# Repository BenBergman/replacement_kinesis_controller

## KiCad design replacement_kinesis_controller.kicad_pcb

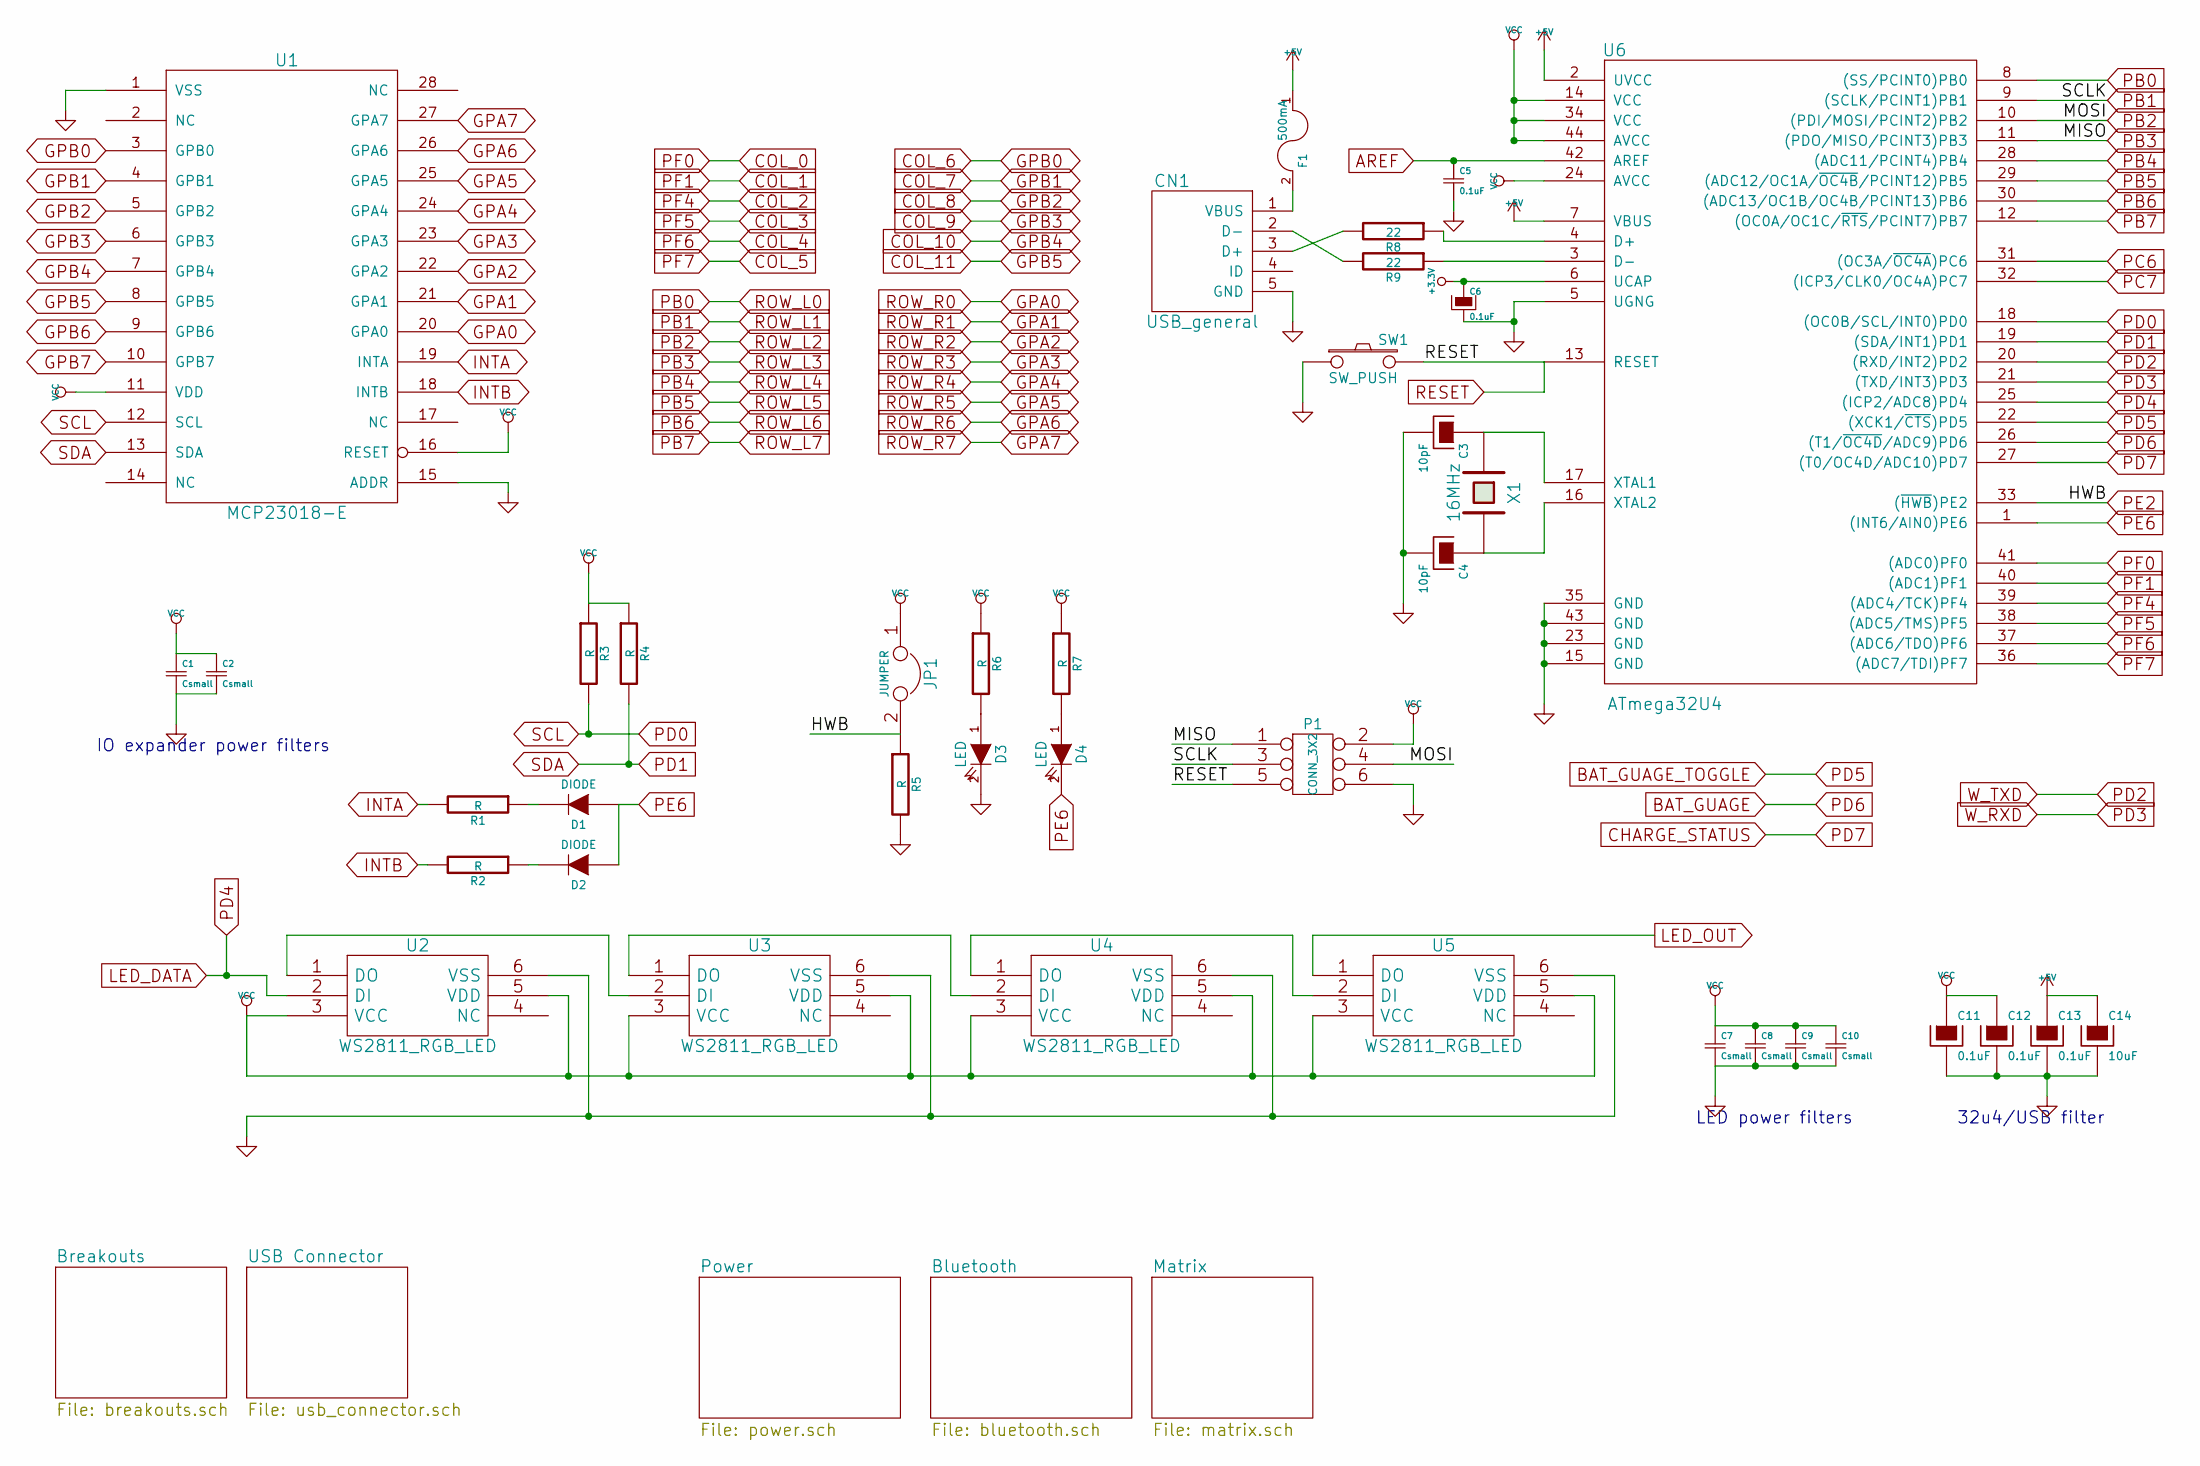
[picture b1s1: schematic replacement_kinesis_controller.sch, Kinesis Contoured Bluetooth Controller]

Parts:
C1, C2, C7, C8, C9, C10: Csmall; C_0805_HandSoldering
C3, C4: 10pF; C_0805_HandSoldering
C5, C6, C11, C12, C13: 0.1uF; C_0805_HandSoldering
C14: 10uF; C_0805_HandSoldering
CN1: USB_general; Pin_Header_Staggered_Straight_1x05
D1, D2: DIODE; SOD-323_Handsolder
D3, D4: LED; LED-0805
F1: 500mA; R_0805_HandSoldering
JP1: JUMPER; JUMPER_2
P1: CONN_3X2; Pin_Header_Staggered_Straight_2x03
R1, R2, R3, R4, R5, R6, R7: R; R_0805_HandSoldering
R8, R9: 22; R_0805_HandSoldering
SW1: SW_PUSH; SW_SPST_PTS645
U1: MCP23018-E; SOIC-28
U2, U3, U4, U5: WS2811_RGB_LED; LED_RGB_WS2811
U6: ATmega32U4; TQFP-44_10x10mm_Pitch0.8mm
X1: 16MHz; Crystal_HC49-SD_SMD

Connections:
+3.3V: C6.1, U6.6 (UCAP); also elsewhere on the board
+5V: C13.1, C14.1, F1.1, U6.2 (UVCC), U6.7 (VBUS); also elsewhere on the board
AREF: C5.1, U6.42 (AREF); also elsewhere on the board
BAT_GUAGE: U6.26 ((T1/~OC4D~/ADC9)PD6); also elsewhere on the board
BAT_GUAGE_TOGGLE: U6.22 ((XCK1/~CTS~)PD5); also elsewhere on the board
COL_0: U6.41 ((ADC0)PF0); also elsewhere on the board
COL_2: U6.39 ((ADC4/TCK)PF4); also elsewhere on the board
COL_5: U6.36 ((ADC7/TDI)PF7); also elsewhere on the board
COL_6: U1.3 (GPB0); also elsewhere on the board
COL_7: U1.4 (GPB1); also elsewhere on the board
COL_8: U1.5 (GPB2); also elsewhere on the board
COL_11: U1.8 (GPB5); also elsewhere on the board
GND: C1.2, C2.2, C3.2, C4.2, C5.2, C6.2, C7.2, C8.2, C9.2, C10.2, C11.2, C12.2, C13.2, C14.2, CN1.5 (GND), D3.2 (K), P1.6, R5.2, SW1.1, U1.1 (VSS), U1.15 (ADDR), U2.6 (VSS), U3.6 (VSS), U4.6 (VSS), U5.6 (VSS), U6.5 (UGNG), U6.15 (GND), U6.23 (GND), U6.35 (GND), U6.43 (GND); also elsewhere on the board
GPA3: U1.23 (GPA3); also elsewhere on the board
GPA5: U1.25 (GPA5); also elsewhere on the board
GPA6: U1.26 (GPA6); also elsewhere on the board
GPA7: U1.27 (GPA7); also elsewhere on the board
GPB3: U1.6 (GPB3); also elsewhere on the board
GPB4: U1.7 (GPB4); also elsewhere on the board
GPB6: U1.9 (GPB6); also elsewhere on the board
GPB7: U1.10 (GPB7); also elsewhere on the board
INTA: R1.2, U1.19 (INTA)
INTB: R2.2, U1.18 (INTB)
LED_OUT: U5.1 (DO); also elsewhere on the board
unnamed: C3.1, U6.17 (XTAL1), X1.1
unnamed: C4.1, U6.16 (XTAL2), X1.2
unnamed: CN1.1 (VBUS), F1.2
unnamed: CN1.2 (D-), R9.2
unnamed: CN1.3 (D+), R8.2
unnamed: D1.2 (K), R1.1
unnamed: D2.2 (K), R2.1
unnamed: D3.1 (A), R6.2
unnamed: D4.1 (A), R7.2
unnamed: R8.1, U6.4 (D+)
unnamed: R9.1, U6.3 (D-)
unnamed: U2.1 (DO), U3.2 (DI)
unnamed: U3.1 (DO), U4.2 (DI)
unnamed: U4.1 (DO), U5.2 (DI)
PB1: P1.3, U6.9 ((SCLK/PCINT1)PB1); also elsewhere on the board
PB2: P1.4, U6.10 ((PDI/MOSI/PCINT2)PB2); also elsewhere on the board
PB3: P1.1, U6.11 ((PDO/MISO/PCINT3)PB3); also elsewhere on the board
PB4: U6.28 ((ADC11/PCINT4)PB4); also elsewhere on the board
PB5: U6.29 ((ADC12/OC1A/~OC4B~/PCINT12)PB5); also elsewhere on the board
PB6: U6.30 ((ADC13/OC1B/OC4B/PCINT13)PB6); also elsewhere on the board
PB7: U6.12 ((OC0A/OC1C/~RTS~/PCINT7)PB7); also elsewhere on the board
PC6: U6.31 ((OC3A/~OC4A~)PC6); also elsewhere on the board
PC7: U6.32 ((ICP3/CLK0/OC4A)PC7); also elsewhere on the board
PD0: R3.2, U1.12 (SCL), U6.18 ((OC0B/SCL/INT0)PD0); also elsewhere on the board
PD3: U6.21 ((TXD/INT3)PD3); also elsewhere on the board
PD7: U6.27 ((T0/OC4D/ADC10)PD7); also elsewhere on the board
PE2: JP1.2, R5.1, U6.33 ((~HWB~)PE2)
PE6: D1.1 (A), D2.1 (A), D4.2 (K), U6.1 ((INT6/AIN0)PE6); also elsewhere on the board
PF1: U6.40 ((ADC1)PF1); also elsewhere on the board
PF5: U6.38 ((ADC5/TMS)PF5); also elsewhere on the board
PF6: U6.37 ((ADC6/TDO)PF6); also elsewhere on the board
RESET: P1.5, SW1.2, U6.13 (RESET); also elsewhere on the board
ROW_L0: U6.8 ((SS/PCINT0)PB0); also elsewhere on the board
ROW_R0: U1.20 (GPA0); also elsewhere on the board
ROW_R1: U1.21 (GPA1); also elsewhere on the board
ROW_R2: U1.22 (GPA2); also elsewhere on the board
ROW_R4: U1.24 (GPA4); also elsewhere on the board
SDA: R4.2, U1.13 (SDA), U6.19 ((SDA/INT1)PD1); also elsewhere on the board
VCC: C1.1, C2.1, C7.1, C8.1, C9.1, C10.1, C11.1, C12.1, JP1.1, P1.2, R3.1, R4.1, R6.1, R7.1, U1.11 (VDD), U1.16 (RESET), U2.3 (VCC), U2.5 (VDD), U3.3 (VCC), U3.5 (VDD), U4.3 (VCC), U4.5 (VDD), U5.3 (VCC), U5.5 (VDD), U6.14 (VCC), U6.24 (AVCC), U6.34 (VCC), U6.44 (AVCC); also elsewhere on the board
W_TXD: U6.20 ((RXD/INT2)PD2); also elsewhere on the board

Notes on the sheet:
32u4/USB filter
LED power filters
IO expander power filters

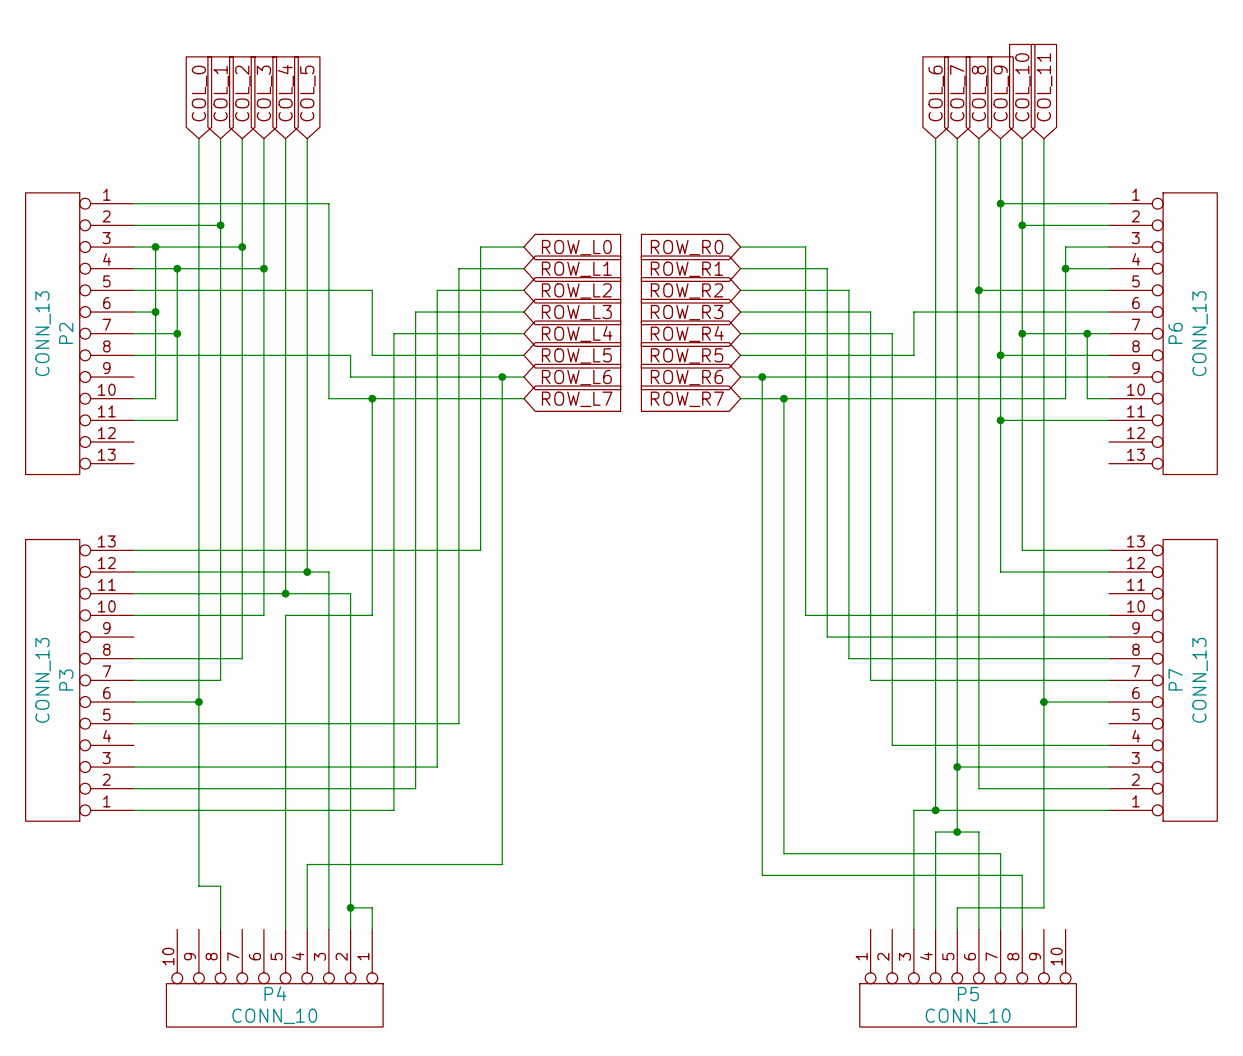
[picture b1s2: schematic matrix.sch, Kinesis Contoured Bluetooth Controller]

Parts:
P2, P7: CONN_13; Molex_FFC_13_mirror
P3, P6: CONN_13; Molex_FFC_13
P4, P5: CONN_10; Pin_Header_Staggered_Straight_1x10

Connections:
COL_0: P3.6, P4.8; also elsewhere on the board
COL_2: P2.3, P2.6, P2.10, P3.8; also elsewhere on the board
COL_5: P3.12, P4.3; also elsewhere on the board
COL_6: P5.3, P7.1; also elsewhere on the board
COL_7: P5.4, P5.6, P7.3; also elsewhere on the board
COL_8: P6.5, P7.2; also elsewhere on the board
COL_11: P5.5, P7.6; also elsewhere on the board
GPA3: P7.7; also elsewhere on the board
GPA5: P6.6; also elsewhere on the board
GPA6: P5.8, P6.9; also elsewhere on the board
GPA7: P5.7, P6.3, P6.4; also elsewhere on the board
GPB3: P6.1, P6.8, P6.11, P7.12; also elsewhere on the board
GPB4: P6.2, P6.7, P6.10, P7.13; also elsewhere on the board
PB1: P3.5; also elsewhere on the board
PB2: P3.3; also elsewhere on the board
PB3: P3.2; also elsewhere on the board
PB4: P3.1; also elsewhere on the board
PB5: P2.5; also elsewhere on the board
PB6: P2.8, P4.4; also elsewhere on the board
PB7: P2.1, P4.5; also elsewhere on the board
PF1: P2.2, P3.7; also elsewhere on the board
PF5: P2.4, P2.7, P2.11, P3.10; also elsewhere on the board
PF6: P3.11, P4.1, P4.2; also elsewhere on the board
ROW_L0: P3.13; also elsewhere on the board
ROW_R0: P7.10; also elsewhere on the board
ROW_R1: P7.9; also elsewhere on the board
ROW_R2: P7.8; also elsewhere on the board
ROW_R4: P7.4; also elsewhere on the board

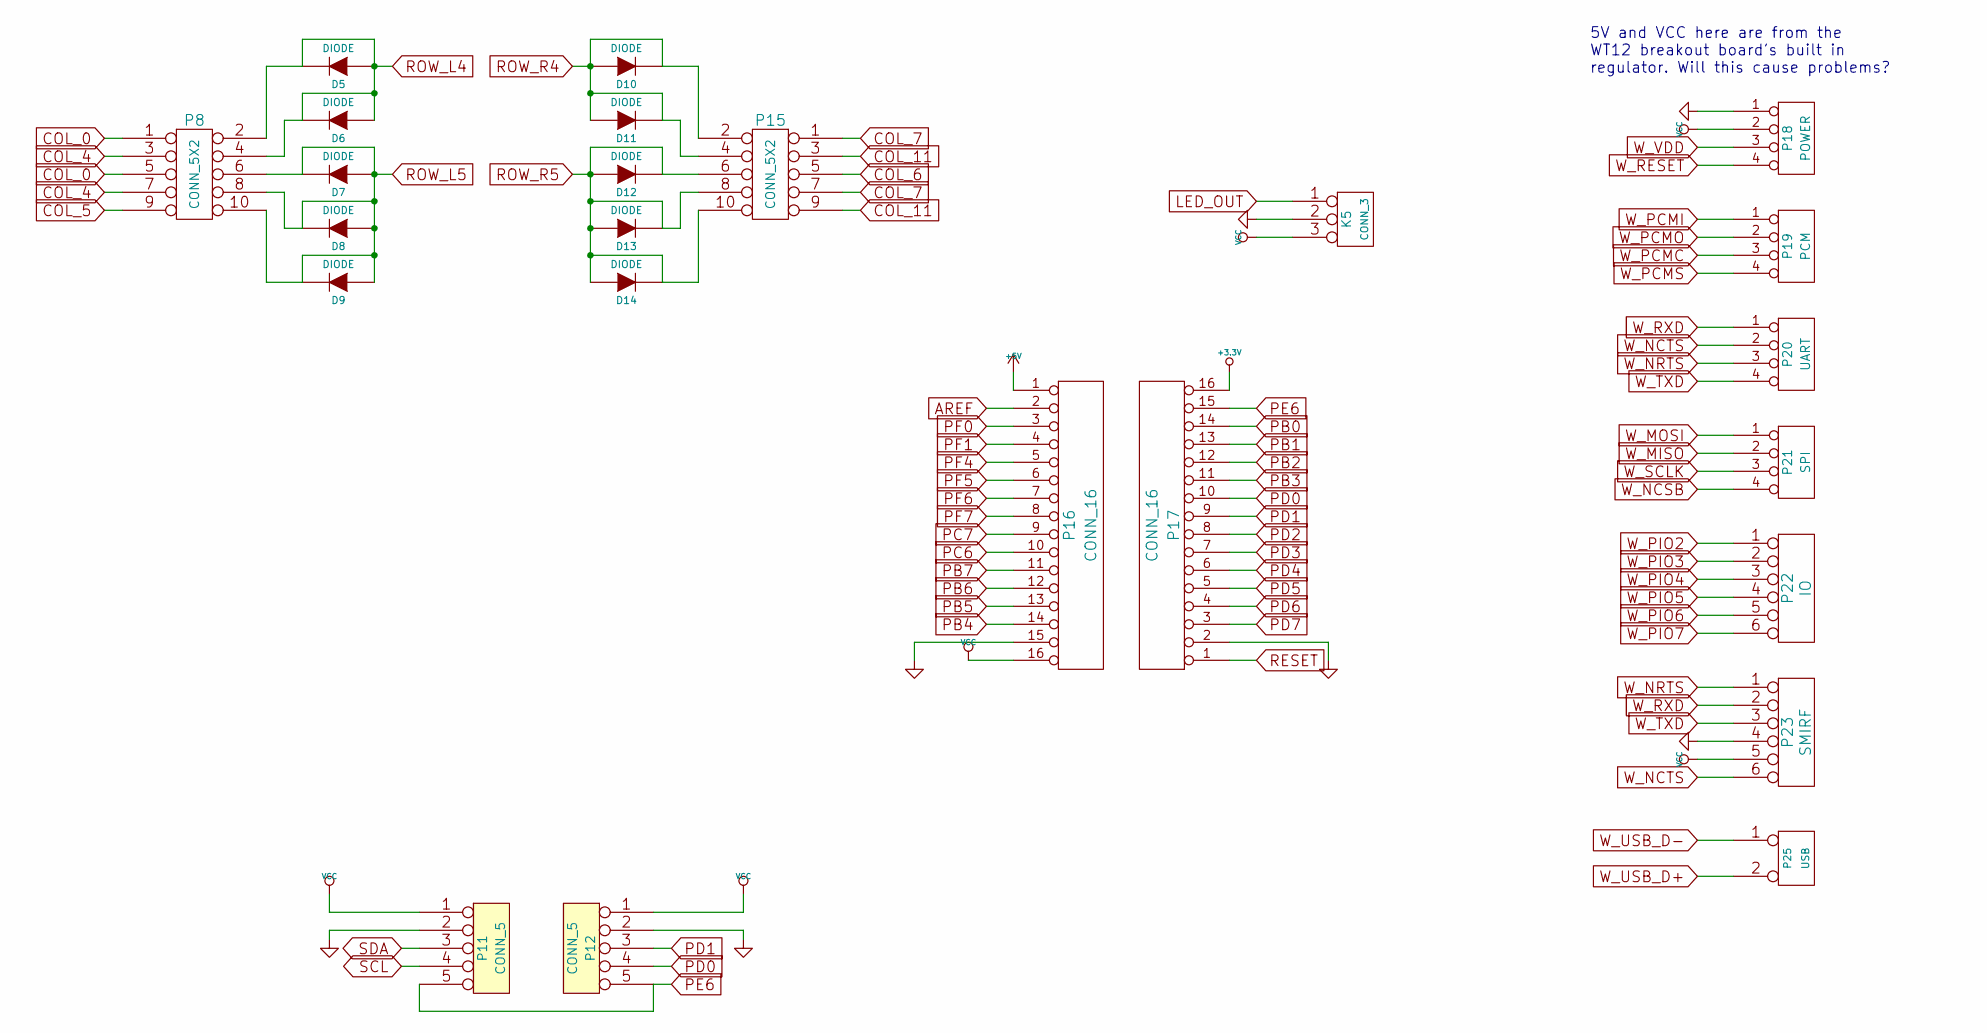
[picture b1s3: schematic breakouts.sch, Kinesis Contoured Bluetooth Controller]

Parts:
D5, D6, D7, D8, D9, D10, D11, D12, D13, D14: DIODE; SOD-323_Handsolder
K5: CONN_3; Pin_Header_Staggered_Straight_1x03
P8, P15: CONN_5X2; Pin_Header_Staggered_Straight_2x05
P11, P12: CONN_5; Pin_Header_Staggered_Straight_1x05
P16, P17: CONN_16; Pin_Header_Staggered_Straight_1x16
P18: POWER; Pin_Header_Staggered_Straight_1x04
P19: PCM; Pin_Header_Staggered_Straight_1x04
P20: UART; Pin_Header_Staggered_Straight_1x04
P21: SPI; Pin_Header_Staggered_Straight_1x04
P22: IO; Pin_Header_Staggered_Straight_1x06
P23: SMIRF; Pin_Header_Staggered_Straight_1x06
P25: USB; Pin_Header_Staggered_Straight_1x02

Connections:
+3.3V: P17.16; also elsewhere on the board
+5V: P16.1; also elsewhere on the board
AREF: P16.2; also elsewhere on the board
BAT_GUAGE: P17.4; also elsewhere on the board
BAT_GUAGE_TOGGLE: P17.5; also elsewhere on the board
COL_0: P8.1, P8.5, P16.3; also elsewhere on the board
COL_2: P16.5; also elsewhere on the board
COL_5: P8.9, P16.8; also elsewhere on the board
COL_6: P15.5; also elsewhere on the board
COL_7: P15.1, P15.7; also elsewhere on the board
COL_11: P15.3, P15.9; also elsewhere on the board
GND: K5.2 (PM), P11.2, P12.2, P16.15, P17.2, P18.1, P23.4; also elsewhere on the board
GPA5: D12.1 (A), D12.2 (K), D13.1 (A), D13.2 (K), D14.1 (A), D14.2 (K), P15.6, P15.8, P15.10; also elsewhere on the board
PB1: P17.13; also elsewhere on the board
PB2: P17.12; also elsewhere on the board
PB3: P17.11; also elsewhere on the board
PB4: D5.1 (A), D5.2 (K), D6.1 (A), D6.2 (K), P8.2, P8.4, P16.14; also elsewhere on the board
PB5: D7.1 (A), D7.2 (K), D8.1 (A), D8.2 (K), D9.1 (A), D9.2 (K), P8.6, P8.8, P8.10, P16.13; also elsewhere on the board
PB6: P16.12; also elsewhere on the board
PB7: P16.11; also elsewhere on the board
PC6: P16.10; also elsewhere on the board
PC7: P16.9; also elsewhere on the board
PD0: P11.4, P12.4, P17.10; also elsewhere on the board
PD3: P17.7, P20.1, P23.2; also elsewhere on the board
PD7: P17.3; also elsewhere on the board
PE6: P11.5, P12.5, P17.15; also elsewhere on the board
PF1: P16.4; also elsewhere on the board
PF5: P16.6; also elsewhere on the board
PF6: P8.3, P8.7, P16.7; also elsewhere on the board
RESET: P17.1; also elsewhere on the board
ROW_L0: P17.14; also elsewhere on the board
ROW_R4: D10.1 (A), D10.2 (K), D11.1 (A), D11.2 (K), P15.2, P15.4; also elsewhere on the board
SDA: P11.3, P12.3, P17.9; also elsewhere on the board
VCC: K5.3, P11.1, P12.1, P16.16, P18.2, P23.5; also elsewhere on the board
W_MISO: P21.2; also elsewhere on the board
W_MOSI: P21.1; also elsewhere on the board
W_NCSB: P21.4; also elsewhere on the board
W_NCTS: P20.2, P23.6; also elsewhere on the board
W_NRTS: P20.3, P23.1; also elsewhere on the board
W_PCMC: P19.3; also elsewhere on the board
W_PCMI: P19.1; also elsewhere on the board
W_PCMO: P19.2; also elsewhere on the board
W_PCMS: P19.4; also elsewhere on the board
W_PIO2: P22.1; also elsewhere on the board
W_PIO3: P22.2; also elsewhere on the board
W_PIO4: P22.3; also elsewhere on the board
W_PIO5: P22.4; also elsewhere on the board
W_PIO6: P22.5; also elsewhere on the board
W_PIO7: P22.6; also elsewhere on the board
W_RESET: P18.4; also elsewhere on the board
W_SCLK: P21.3; also elsewhere on the board
W_TXD: P17.8, P20.4, P23.3; also elsewhere on the board
W_USB_D+: P25.2 (PM); also elsewhere on the board
W_USB_D-: P25.1; also elsewhere on the board
W_VDD: P18.3; also elsewhere on the board

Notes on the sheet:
5V and VCC here are from the WT12 breakout board's built in regulator. Will this cause problems?

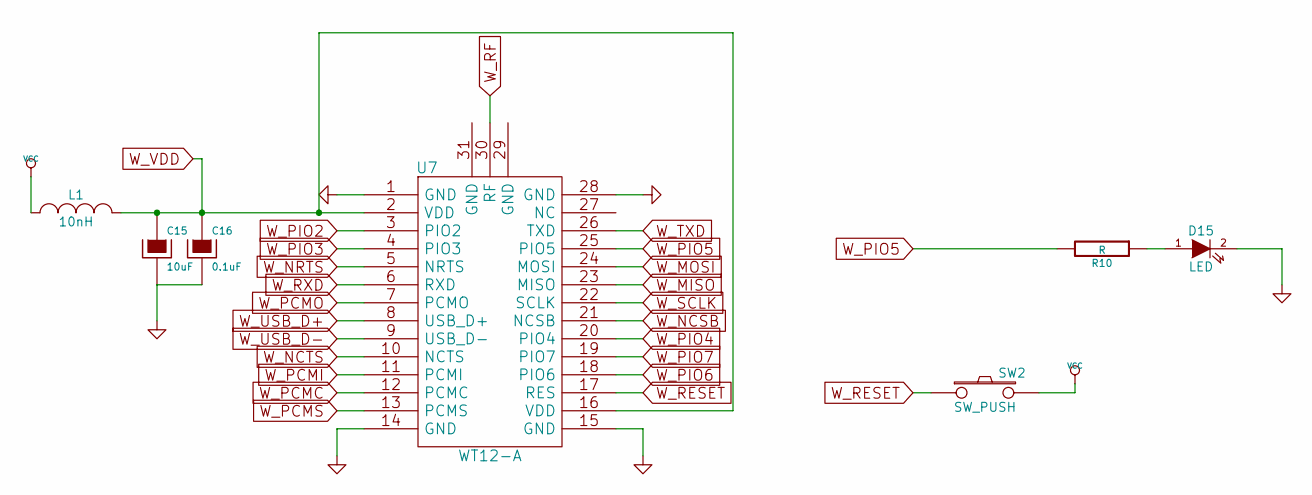
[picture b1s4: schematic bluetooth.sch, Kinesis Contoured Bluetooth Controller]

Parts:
C15: 10uF; C_0805_HandSoldering
C16: 0.1uF; C_0805_HandSoldering
D15: LED; LED-0805
L1: 10nH; R_0805_HandSoldering
R10: R; R_0805_HandSoldering
SW2: SW_PUSH; SW_SPST_PTS645
U7: WT12-A; WT12

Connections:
GND: C15.2, C16.2, D15.2 (K), U7.1 (GND), U7.14 (GND), U7.15 (GND), U7.28 (GND); also elsewhere on the board
unnamed: D15.1 (A), R10.1
PD3: U7.6 (RXD); also elsewhere on the board
VCC: L1.1, SW2.2; also elsewhere on the board
W_MISO: U7.23 (MISO); also elsewhere on the board
W_MOSI: U7.24 (MOSI); also elsewhere on the board
W_NCSB: U7.21 (NCSB); also elsewhere on the board
W_NCTS: U7.10 (NCTS); also elsewhere on the board
W_NRTS: U7.5 (NRTS); also elsewhere on the board
W_PCMC: U7.12 (PCMC); also elsewhere on the board
W_PCMI: U7.11 (PCMI); also elsewhere on the board
W_PCMO: U7.7 (PCMO); also elsewhere on the board
W_PCMS: U7.13 (PCMS); also elsewhere on the board
W_PIO2: U7.3 (PIO2); also elsewhere on the board
W_PIO3: U7.4 (PIO3); also elsewhere on the board
W_PIO4: U7.20 (PIO4); also elsewhere on the board
W_PIO5: R10.2, U7.25 (PIO5); also elsewhere on the board
W_PIO6: U7.18 (PIO6); also elsewhere on the board
W_PIO7: U7.19 (PIO7); also elsewhere on the board
W_RESET: SW2.1, U7.17 (RES); also elsewhere on the board
W_RF: U7.30 (RF)
W_SCLK: U7.22 (SCLK); also elsewhere on the board
W_TXD: U7.26 (TXD); also elsewhere on the board
W_USB_D+: U7.8 (USB_D+); also elsewhere on the board
W_USB_D-: U7.9 (USB_D-); also elsewhere on the board
W_VDD: C15.1, C16.1, L1.2, U7.2 (VDD), U7.16 (VDD); also elsewhere on the board

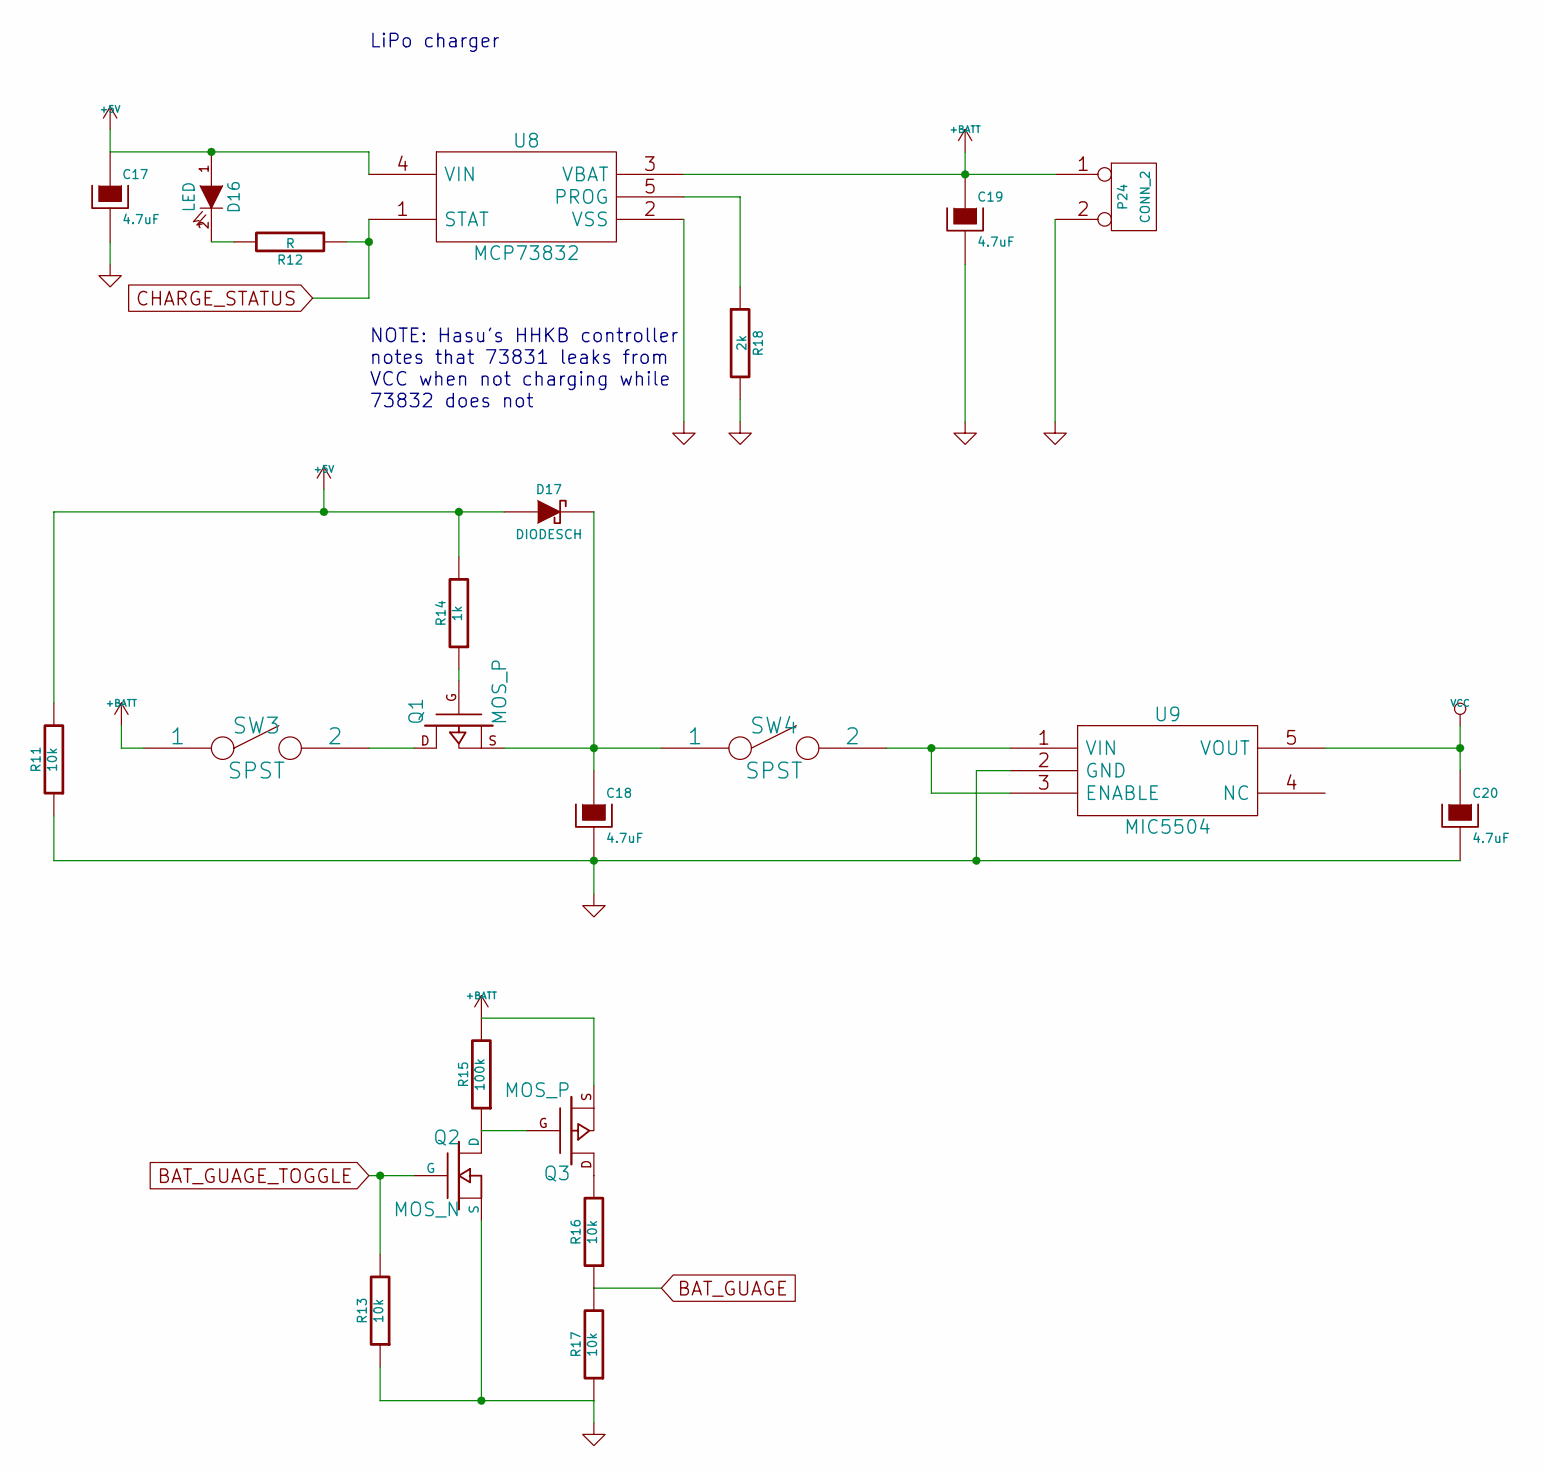
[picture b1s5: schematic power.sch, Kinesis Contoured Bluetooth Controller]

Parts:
C17, C18, C19, C20: 4.7uF; C_0805_HandSoldering
D16: LED; LED-0805
D17: DIODESCH; SOD-123_Handsolder
P24: CONN_2; JST-2
Q1, Q3: MOS_P; SOT23_Handsoldering
Q2: MOS_N; SOT23_Handsoldering
R11, R13, R16, R17: 10k; R_0805_HandSoldering
R12: R; R_0805_HandSoldering
R14: 1k; R_0805_HandSoldering
R15: 100k; R_0805_HandSoldering
R18: 2k; R_0805_HandSoldering
SW3, SW4: SPST; Pin_Header_Staggered_Straight_1x02
U8: MCP73832; SOT23-5_handsolder
U9: MIC5504; SOT23-5_handsolder

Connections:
+5V: C17.1, D16.1 (A), D17.1 (A), R11.2, R14.2, U8.4 (VIN); also elsewhere on the board
+BATT: C19.1, P24.1, Q3.S, R15.2, SW3.1, U8.3 (VBAT)
BAT_GUAGE: R16.1, R17.2; also elsewhere on the board
BAT_GUAGE_TOGGLE: Q2.G, R13.2; also elsewhere on the board
GND: C17.2, C18.2, C19.2, C20.2, P24.2 (PM), Q2.S, R11.1, R13.1, R17.1, R18.2, U8.2 (VSS), U9.2 (GND); also elsewhere on the board
unnamed: C18.1, D17.2 (K), Q1.S, SW4.1
unnamed: D16.2 (K), R12.2
unnamed: Q1.D, SW3.2
unnamed: Q1.G, R14.1
unnamed: Q2.D, Q3.G, R15.1
unnamed: Q3.D, R16.2
unnamed: R18.1, U8.5 (PROG)
unnamed: SW4.2, U9.1 (VIN), U9.3 (ENABLE)
PD7: R12.1, U8.1 (STAT); also elsewhere on the board
VCC: C20.1, U9.5 (VOUT); also elsewhere on the board

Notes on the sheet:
LiPo charger
NOTE: Hasu's HHKB controller notes that 73831 leaks from VCC when not charging while 73832 does not

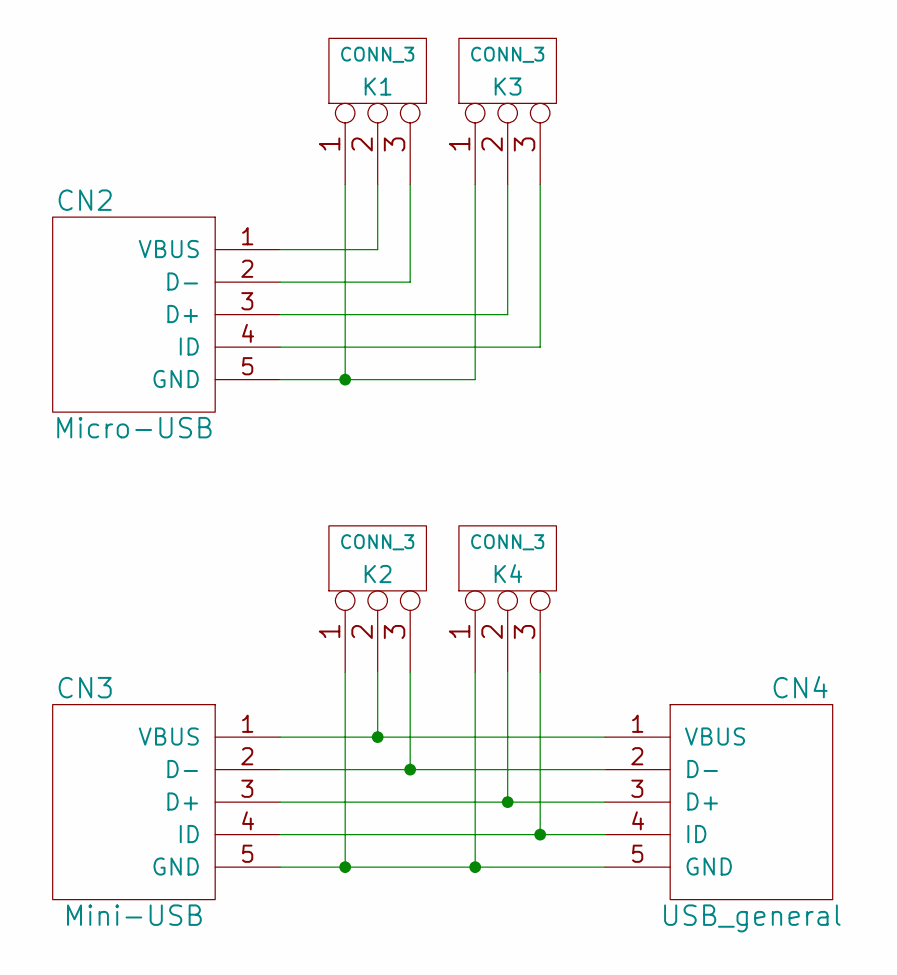
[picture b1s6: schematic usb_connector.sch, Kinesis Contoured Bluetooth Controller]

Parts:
CN2: Micro-USB; USB_micro_B-vertical
CN3: Mini-USB; USB_mini_B-vertical
CN4: USB_general; Pin_Header_Staggered_Straight_1x05
K1, K2, K3, K4: CONN_3; Pin_Header_Staggered_Straight_1x03

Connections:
unnamed: CN2.1 (VBUS), K1.2 (PM)
unnamed: CN2.2 (D-), K1.3
unnamed: CN2.3 (D+), K3.2 (PM)
unnamed: CN2.4 (ID), K3.3
unnamed: CN2.5 (GND), K1.1, K3.1
unnamed: CN3.1 (VBUS), CN4.1 (VBUS), K2.2 (PM)
unnamed: CN3.2 (D-), CN4.2 (D-), K2.3
unnamed: CN3.3 (D+), CN4.3 (D+), K4.2 (PM)
unnamed: CN3.4 (ID), CN4.4 (ID), K4.3
unnamed: CN3.5 (GND), CN4.5 (GND), K2.1, K4.1

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
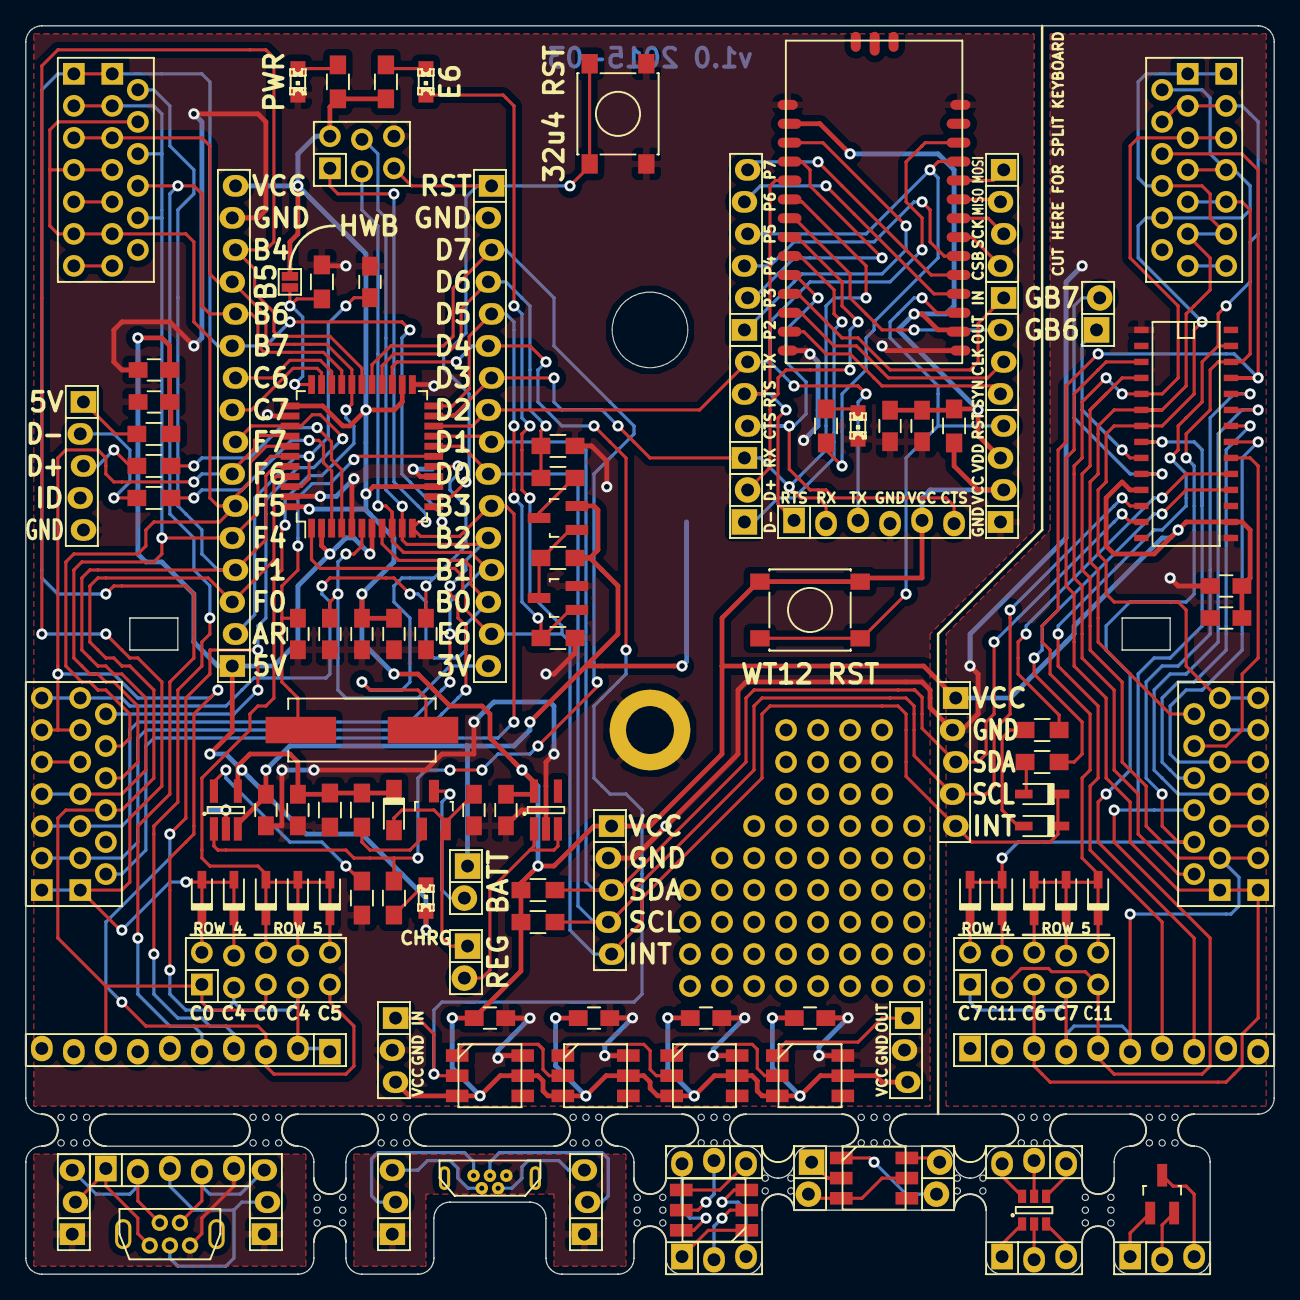
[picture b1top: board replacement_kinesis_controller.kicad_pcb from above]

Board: 2 copper layers, 99.1 x 99.1 mm, 118 parts (1 on the bottom side), 105 nets.

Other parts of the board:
K5#2: CONN_3; Pin_Header_Staggered_Straight_1x03
MountingHole_6mm: VAL**; MountingHole_6mm
Pin_Header_Staggered_Straight_1x02, Pin_Header_Staggered_Straight_1x02#2, Pin_Header_Staggered_Straight_1x02#3: VAL**; Pin_Header_Staggered_Straight_1x02
Pin_Header_Staggered_Straight_1x03, Pin_Header_Staggered_Straight_1x03#2, Pin_Header_Staggered_Straight_1x03#3, Pin_Header_Staggered_Straight_1x03#4, Pin_Header_Staggered_Straight_1x03#5: VAL**; Pin_Header_Staggered_Straight_1x03
Pin_Header_Straight_1x01: VAL**; Plated_Mounting_Hole
SOT23-6_1: VAL**; SOT23-6
SOT-23_HandSoldering: VAL**; SOT-23_Handsoldering

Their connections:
GND: K5#2.2, Pin_Header_Straight_1x01.1; also elsewhere on the board
GPB6: Pin_Header_Staggered_Straight_1x02#3.1; also elsewhere on the board
GPB7: Pin_Header_Staggered_Straight_1x02#3.2; also elsewhere on the board
LED_OUT: K5#2.1; also elsewhere on the board
VCC: K5#2.3; also elsewhere on the board

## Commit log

2014-12-10 Updated schematic with matrix info
2015-01-28 Fix up right function key matrix
2015-01-29 Add value and extras for 32u4 breakout schematic
2015-01-30 Add IO expander
2015-01-30 Add matrix to IO map
2015-02-02 Add lipo charging circuitry
2015-02-02 Add battery connector (should be JST connector)
2015-02-03 Add WT12 symbol
2015-02-03 Add all bluetooth headers
2015-02-06 More stuff, including LEDs
2015-02-07 Add some connections and many headers
2015-02-07 Connect ATmega to WT12
2015-02-07 Reorganize and fix USB breakout
2015-02-07 Add battery guage circuitry
2015-02-07 Add voltage regulation
2015-02-08 Add breakouts for empty sections of switch matrix
2015-02-11 Add some design notes
2015-02-12 Add pull up resistors to i2c line (TWCR wait loop stuck otherwise)
2015-02-14 Add note about lipo stuff
2015-02-18 Fix right function keys wiring
2015-02-18 Restructure some things into sheets
2015-02-18 Fix new VCC pin to use power symbol
2015-02-19 Sort remaining sections to sheets
2015-02-20 Assign RGB LEDs a pin
2015-02-20 Add power filters for LEDs
2015-02-20 Move some stuff around and add reset button to WT12
2015-02-20 Switch LEDs to another pin to free the remaining interrupt pin
2015-02-20 Add MCP23018 interrupt connections
2015-02-20 Correct diode polarity for external switches
2015-02-21 Add power switch
2015-02-21 Add connections from battery monitoring circuitry to 32u4
2015-02-21 Add capacitor to AREF line, similar to Hasu's controller
2015-02-21 Switch HWB to a pull down and open jumper to hopefully reduce power consumption
2015-02-21 Move Bluetooth wire assignment to front sheet
2015-02-21 Change voltage source auto switch over circuitry to match Hasu's
2015-02-21 Correct circuit for battery monitoring
2015-02-21 Add pull-down resistor to bat gauge circuit to match Hasu's
2015-02-21 Add secondary power switch location
2015-02-21 Add note about bluetooth power breakout
2015-02-21 Add PIO5 LED to WT12 circuit like the breakoutboard has
2015-02-21 Update sheet fields
2015-02-21 Add missing usb connector sheet
2015-02-22 Add a whole bunch of new footprints
2015-02-22 Ignore auto generated files and backups
2015-02-22 Add start of pcb layout (mounting points and netlist import)
2015-02-22 Add annotations to parts
2015-02-22 Spread out components
2015-02-22 Matrix connectors in place
2015-02-22 Add component footprint map
2015-02-22 Add RGB LEDs
2015-02-22 Add RGB LED footprint
2015-02-22 Some changes to PCB
2015-02-22 WT12 breakout headers are now in place
2015-02-23 Add footprints to regular diodes
2015-02-23 Add regular LED footprints
2015-02-23 Add diode footprints
2015-02-23 More footprints
2015-02-23 Add modules for vertical USB connectors
2015-02-23 Add usb footprints
2015-02-23 Move footprints around
2015-02-23 Add mockup of USB breakout
2015-02-24 Add more footprint mappings
2015-02-24 Add WT12 footprint
2015-02-24 Basically done footprint assignment now...?
2015-02-24 Load last set of footprints
2015-02-24 Fix WT12 footprint
2015-02-24 A bunch of footprint arranging
2015-02-24 Add netlist in case it is important to track, even though it is auto generated
2015-02-25 Started laying some tracks
2015-02-26 Ran a bunch of IO expander matrix tracks
2015-02-26 Right half of matrix basically done
2015-02-26 Power supply and LED tracks placed
2015-02-27 Ran a bunch of tracks for the 32u4
2015-02-27 More 32u4 traces
2015-02-27 Some left matrix traces
2015-02-27 Matrix and WT12 basically done
2015-02-28 More WT12 wiring
2015-03-03 Initial run of I2C lines
2015-03-04 Rearranged some traces
2015-03-04 Shoehorned another cap into the 32u4 breakout area
2015-03-04 Add power switch connectors
2015-03-07 Update bom and add a bunch of layout stuff
2015-03-07 A bunch more rejiggering
2015-03-08 More traces laid
2015-03-08 Add a bunch of breakout boards in dead space
2015-03-08 Fix edge cuts
2015-03-08 Fixed mounting slot positions
2015-03-08 Moved edge traces slightly more inbound
2015-03-13 Round corners of breakout boards and add mouse bites
2015-03-13 Round corners of main PCB
2015-03-14 Lots of adjustments to fit in ground pour
2015-03-14 Fix bluetooth breakout pin nets and add ground pour to USB boards
2015-03-14 Add breakout for LED chain output
2015-03-14 Clean up silk screen, etc.
2015-03-14 Add a bunch of silk screen stuff
2015-03-15 More silkscreen stuff
2015-03-15 Rearrange stuff so as to breakout IO expander pins
2015-03-15 Add labels for IO expander breakout pins
2015-03-15 Remove most solder jumpers
2015-03-15 Fix USB pin order on main connector
2015-03-15 Remove last solder jumper from PCB
2015-03-15 Label reset switches on silk screen
2015-03-15 Rejigger things to make board more easily separable
2015-03-18 A bunch of silkscreen improvements
2015-03-18 Update sot23-5 footprint for handsoldering
2015-03-18 More silk updates and another WS2811 breakout
2015-03-18 Remove matrix breakout connectors
2015-03-19 Add some perfboard in dead space
2015-03-19 Add perf board footprint
2015-03-19 Change via drill size
2015-03-19 Increase diode pad size for handsoldering
2015-03-20 Resize one text element to fit a bit cleaner
2015-03-22 Add slots to drill layer
